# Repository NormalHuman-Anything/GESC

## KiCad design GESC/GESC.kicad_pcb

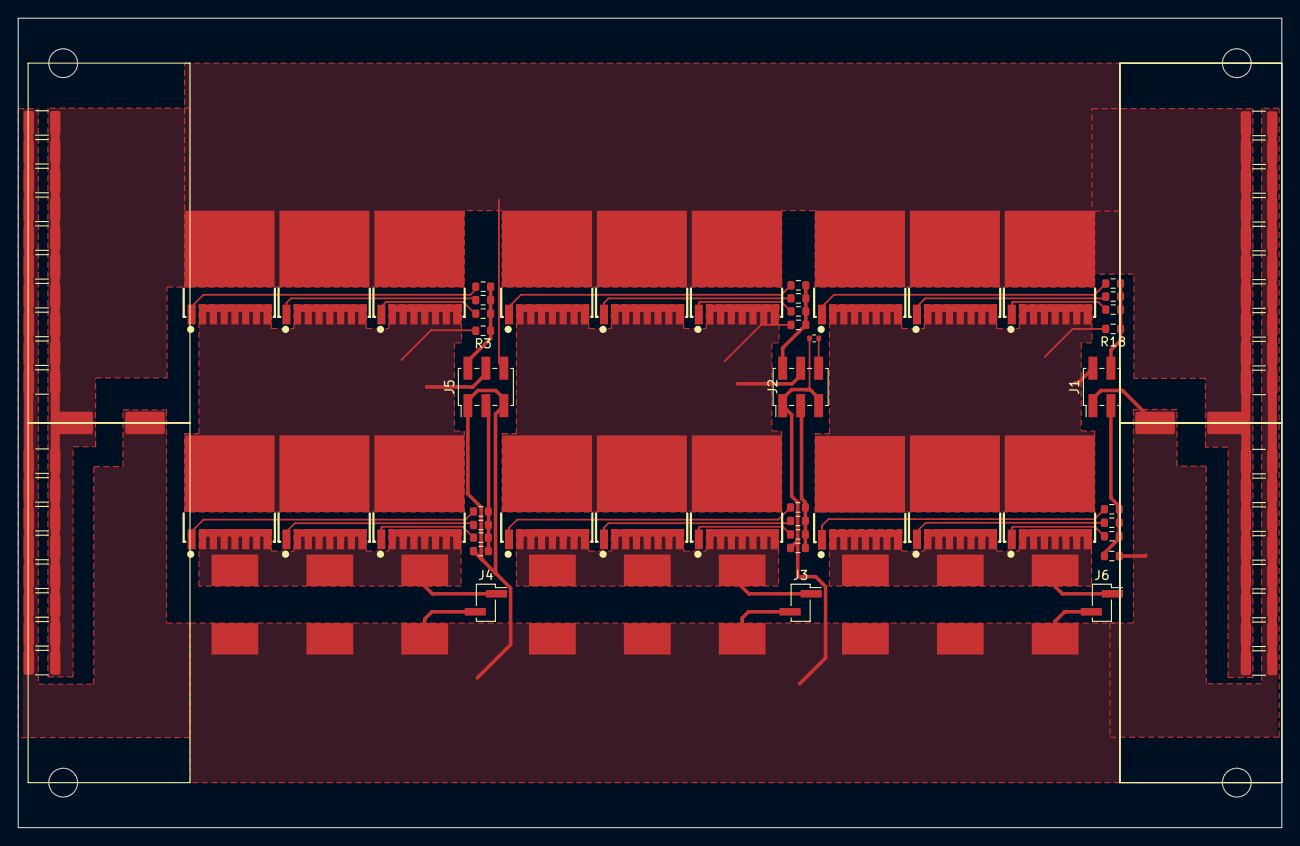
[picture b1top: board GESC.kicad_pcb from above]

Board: 4 copper layers, 140.5 x 90.0 mm, 94 parts (0 on the bottom side), 33 nets.

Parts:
C1, C1#2, C2, C2#2, C3, C3#2, C4, C4#2, C5, C5#2, C6, C6#2, C7, C7#2, C8, C8#2, C9, C9#2, C10, C10#2, C15, C15#2, C16, C16#2, C17, C18, C18#2, C19, C20, C21, C22, C22#2, C23, C23#2, C24, C24#2: 470nF; C_1210_3225Metric
J1: gates_A; PinHeader_2x02_P2.00mm_Vertical_SMD
J2: gates_B; PinHeader_2x03_P2.00mm_Vertical_SMD
J3: SH2; PinHeader_1x02_P2.00mm_Vertical_SMD_Pin1Right
J4: SH1; PinHeader_1x02_P2.00mm_Vertical_SMD_Pin1Right
J5: gates_C; PinHeader_2x03_P2.00mm_Vertical_SMD
J6: SH3; PinHeader_1x02_P2.00mm_Vertical_SMD_Pin1Right
Q1, Q2, Q3, Q4, Q5, Q6, Q7, Q8, Q9, Q10, Q11, Q12, Q13, Q14, Q15, Q16, Q17, Q18: TOLL; TOLL-8_L10.4-W9.9-P1.20-LS11.7-BL
R1, R2, R7, R8, R10, R11, R14, R15, R48, R49, R50, R51, R53, R54, R56, R57, R59, R60: 4R7; R_0603_1608Metric
R3, R4, R5, R6, R18, R47: 10k; R_0603_1608Metric
R9, R12, R13, R16, R17, R52, R55, R58, R61: 0.2mR; R3920
TH1: 10k ntc; R_0402_1005Metric

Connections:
+BATT: C1.1, C1#2.1, C2.1, C2#2.1, C3.1, C3#2.1, C4.1, C4#2.1, C5.1, C5#2.1, C6.1, C6#2.1, C7.1, C7#2.1, C8.1, C8#2.1, C9.1, C9#2.1, C10.1, C10#2.1, C15.1, C15#2.1, C16.1, C16#2.1, C17.1, C18.1, C18#2.1, C19.1, C20.1, C21.1, C22.1, C22#2.1, C23.1, C23#2.1, C24.1, C24#2.1, J5.6, Q1.9 (D), Q2.9 (D), Q3.9 (D), Q7.9 (D), Q9.9 (D), Q11.9 (D), Q13.9 (D), Q15.9 (D), Q17.9 (D)
GND: C1.2, C1#2.2, C2.2, C2#2.2, C3.2, C3#2.2, C4.2, C4#2.2, C5.2, C5#2.2, C6.2, C6#2.2, C7.2, C7#2.2, C8.2, C8#2.2, C9.2, C9#2.2, C10.2, C10#2.2, C15.2, C15#2.2, C16.2, C16#2.2, C17.2, C18.2, C18#2.2, C19.2, C20.2, C21.2, C22.2, C22#2.2, C23.2, C23#2.2, C24.2, C24#2.2, J1.1, J2.1, J2.5, J3.2, J4.2, J5.1, J5.5, J6.2, R4.2, R6.2, R9.2, R12.2, R13.2, R16.2, R17.2, R47.2, R52.2, R55.2, R58.2, R61.2, TH1.1
unnamed: J1.3, R47.1, R51.1, R57.1, R60.1
unnamed: J1.4, R18.1, R48.1, R56.1, R59.1
unnamed: J2.2, R5.1, R7.1, R10.1, R14.1
unnamed: J2.3, R6.1, R8.1, R11.1, R15.1
unnamed: J2.6, TH1.2
unnamed: J3.1, Q8.2 (S), Q8.3 (S), Q8.4 (S), Q8.5 (S), Q8.6 (S), Q8.7 (S), Q8.8 (S), Q10.2 (S), Q10.3 (S), Q10.4 (S), Q10.5 (S), Q10.6 (S), Q10.7 (S), Q10.8 (S), Q12.2 (S), Q12.3 (S), Q12.4 (S), Q12.5 (S), Q12.6 (S), Q12.7 (S), Q12.8 (S), R9.1, R12.1, R17.1
unnamed: J4.1, Q4.2 (S), Q4.3 (S), Q4.4 (S), Q4.5 (S), Q4.6 (S), Q4.7 (S), Q4.8 (S), Q5.2 (S), Q5.3 (S), Q5.4 (S), Q5.5 (S), Q5.6 (S), Q5.7 (S), Q5.8 (S), Q6.2 (S), Q6.3 (S), Q6.4 (S), Q6.5 (S), Q6.6 (S), Q6.7 (S), Q6.8 (S), R13.1, R16.1, R55.1
unnamed: J5.2, R1.1, R3.1, R49.1, R53.1
unnamed: J5.3, R2.1, R4.1, R50.1, R54.1
unnamed: J6.1, Q14.2 (S), Q14.3 (S), Q14.4 (S), Q14.5 (S), Q14.6 (S), Q14.7 (S), Q14.8 (S), Q16.2 (S), Q16.3 (S), Q16.4 (S), Q16.5 (S), Q16.6 (S), Q16.7 (S), Q16.8 (S), Q18.2 (S), Q18.3 (S), Q18.4 (S), Q18.5 (S), Q18.6 (S), Q18.7 (S), Q18.8 (S), R52.1, R58.1, R61.1
unnamed: Q1.1 (G), R1.2
unnamed: Q2.1 (G), R49.2
unnamed: Q3.1 (G), R53.2
unnamed: Q4.1 (G), R2.2
unnamed: Q5.1 (G), R50.2
unnamed: Q6.1 (G), R54.2
unnamed: Q7.1 (G), R7.2
unnamed: Q8.1 (G), R8.2
unnamed: Q9.1 (G), R10.2
unnamed: Q10.1 (G), R11.2
unnamed: Q11.1 (G), R14.2
unnamed: Q12.1 (G), R15.2
unnamed: Q13.1 (G), R48.2
unnamed: Q14.1 (G), R51.2
unnamed: Q15.1 (G), R56.2
unnamed: Q16.1 (G), R57.2
unnamed: Q17.1 (G), R59.2
unnamed: Q18.1 (G), R60.2
Phase_A: J5.4, Q1.2 (S), Q1.3 (S), Q1.4 (S), Q1.5 (S), Q1.6 (S), Q1.7 (S), Q1.8 (S), Q2.2 (S), Q2.3 (S), Q2.4 (S), Q2.5 (S), Q2.6 (S), Q2.7 (S), Q2.8 (S), Q3.2 (S), Q3.3 (S), Q3.4 (S), Q3.5 (S), Q3.6 (S), Q3.7 (S), Q3.8 (S), Q4.9 (D), Q5.9 (D), Q6.9 (D), R3.2
Phase_B: J2.4, Q7.2 (S), Q7.3 (S), Q7.4 (S), Q7.5 (S), Q7.6 (S), Q7.7 (S), Q7.8 (S), Q8.9 (D), Q9.2 (S), Q9.3 (S), Q9.4 (S), Q9.5 (S), Q9.6 (S), Q9.7 (S), Q9.8 (S), Q10.9 (D), Q11.2 (S), Q11.3 (S), Q11.4 (S), Q11.5 (S), Q11.6 (S), Q11.7 (S), Q11.8 (S), Q12.9 (D), R5.2
Phase_C: J1.2, Q13.2 (S), Q13.3 (S), Q13.4 (S), Q13.5 (S), Q13.6 (S), Q13.7 (S), Q13.8 (S), Q14.9 (D), Q15.2 (S), Q15.3 (S), Q15.4 (S), Q15.5 (S), Q15.6 (S), Q15.7 (S), Q15.8 (S), Q16.9 (D), Q17.2 (S), Q17.3 (S), Q17.4 (S), Q17.5 (S), Q17.6 (S), Q17.7 (S), Q17.8 (S), Q18.9 (D), R18.2

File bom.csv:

"Reference","Value","Datasheet","Footprint","Qty","DNP","LCSC Part"
"C15,C16,C17,C18,C19,C20,C21,C22,C23,C24","470nF","~","Capacitor_SMD:C_1210_3225Metric","10","","C192761"
"C25,C26,C27,C28","330uF","~","lcsc:CAP-SMD_BD12.5-L13.5-W13.5-FD-1","4","","C487184"
"J1","gates_A","~","Connector_PinHeader_2.00mm:PinHeader_2x02_P2.00mm_Vertical_SMD","1","DNP",""
"J2","gates_B","~","Connector_PinHeader_2.00mm:PinHeader_2x03_P2.00mm_Vertical_SMD","1","DNP",""
"J3","SH2","~","Connector_PinHeader_2.00mm:PinHeader_2x01_P2.00mm_Vertical_SMD","1","DNP",""
"J4,J17,J18,J19","SH1","~","-- mixed values --","4","DNP",""
"J5","gates_C","~","Connector_PinHeader_2.00mm:PinHeader_2x03_P2.00mm_Vertical_SMD","1","DNP",""
"J6","SH3","~","Connector_PinHeader_2.00mm:PinHeader_2x01_P2.00mm_Vertical_SMD","1","DNP",""
"Q1,Q2,Q3,Q4,Q5,Q6,Q7,Q8,Q9,Q10,Q11,Q12,Q13,Q14,Q15,Q16,Q17,Q18","TOLL","https://www.infineon.com/dgdl/irfp4668pbf.pdf?fileId=5546d46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","lcsc:TOLL-8_L10.4-W9.9-P1.20-LS11.7-BL","18","","C2979263"
"R1,R2,R7,R8,R10,R11,R14,R15,R48,R49,R50,R51,R53,R54,R56,R57,R59,R60","4R7","~","Resistor_SMD:R_0603_1608Metric","18","","C23164"
"R3,R4,R5,R6,R18,R47","10k","~","Resistor_SMD:R_0603_1608Metric","6","","C2930027"
"R9,R12,R13,R16,R17,R52,R55,R58,R61","0.5mR","~","lcsc:R3920","9","","C5224155"
"TH1","100k NTC","~","Resistor_SMD:R_0402_1005Metric","1","","C77130"

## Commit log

2024-10-10 aaaaaaaaaaaaaaaaaaa
2024-10-11 ninebot style conn
2024-11-27 full to power board only
2024-12-27 final before shortening
2025-01-25 asdf
2025-01-27 Update LICENSE
2025-05-05 final
